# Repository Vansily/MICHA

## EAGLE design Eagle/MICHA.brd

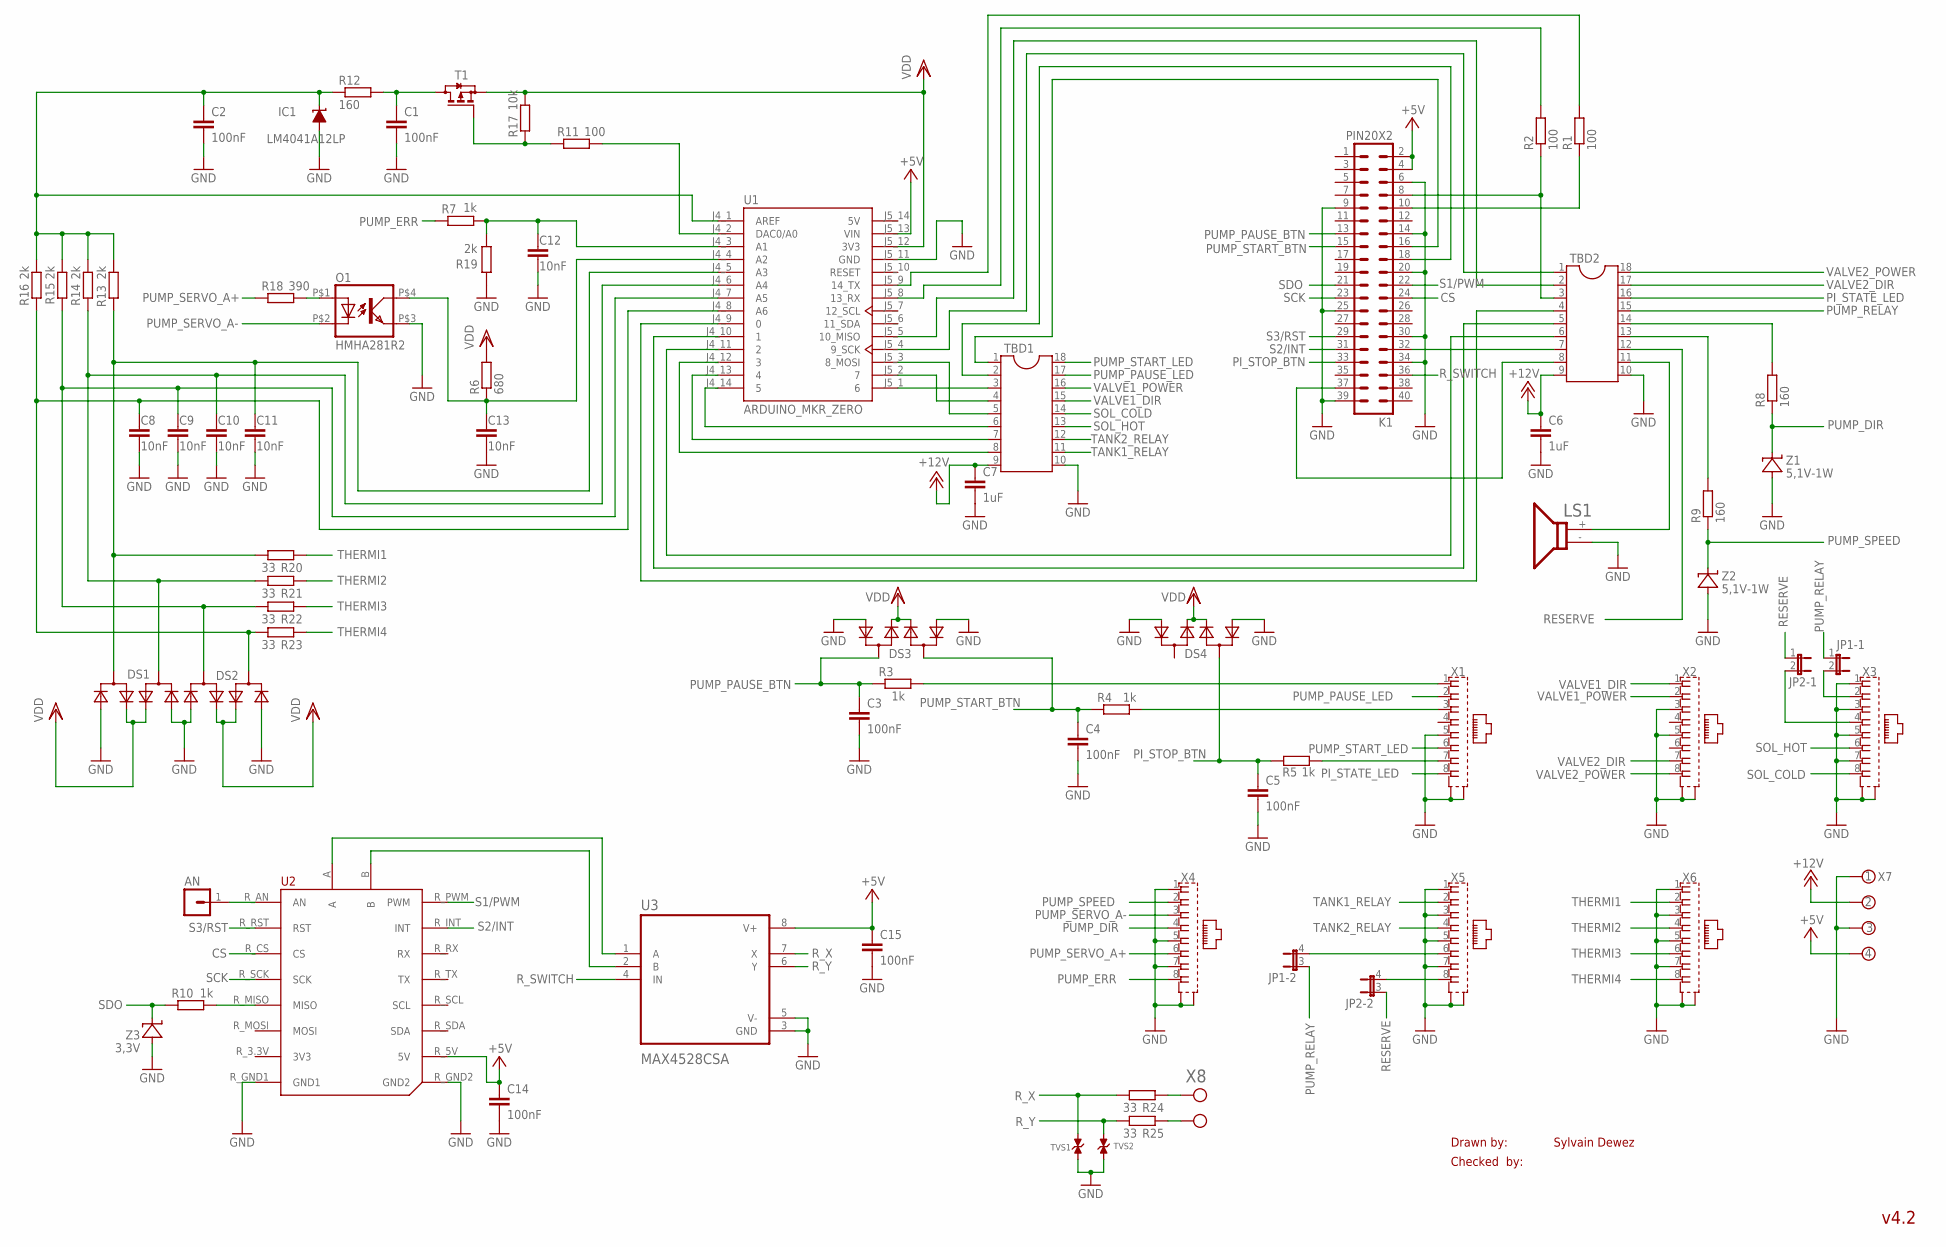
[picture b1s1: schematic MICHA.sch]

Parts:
AN: MA01_PINHEADER; MA01
C1, C2, C3, C4, C5, C14, C15: 100nF; C1206
C6, C7: 1uF; C1206
C8, C9, C10, C11, C12, C13: 10nF; C1206
DS1, DS2, DS3, DS4: SDM10M45SD; SDM10M45SD_SOT-26
IC1: LM4041A12LP; LP_O-PBCY-W3
JP1, JP2: JP2QE; JP2Q
K1: PIN20X2; PIN_20X2
LS1: RSPRO-BUZZER-7800743
O1: HMHA281R2
R1, R2, R11: 100; R1206
R3, R4, R5, R7, R10: 1k; R1206
R6: 680; R1206
R8, R9, R12: 160; R1206
R13, R14, R15, R16, R19: 2k; R1206
R17: 10k; R1206
R18: 390; R1206
R20, R21, R22, R23, R24, R25: 33; R1206
T1: BSS84; SOT23
TBD1, TBD2: DIL18S; SOCKET-18
TVS1, TVS2: TVS_SOD123
U1: ARDUINO_MKR_ZERO; MODULE_ARDUINO_MKR_ZERO
U2: MIKROE_CLICK_UPGRADE; MIKROE_BUS_MIDI_UPGRADE
U3: MAX4528CSA; SOIC127P600X175-8N
X1, X2, X3, X4, X5, X6: SS-7188S-A-NF_V2; BEL_SS-7188S-A-NF
X7: BUCHANAN_4_3.5MM
X8: MPT_0,5/_2-2,54_1725656_2; PH_MPT_0,5/_2-2,54_1725656
Z1, Z2: 5,1V-1W; ZENER_SMA
Z3: 3,3V; ZENER_SMA

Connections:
5V: U1.J5_14 (5V)
+5V: C14.1, C15.1, K1.2, K1.4, U1.J5_13 (VIN), U2.R_5V (5V), U3.8 (V+), X7.4 (KL3)
+12V: C6.1, C7.1, TBD1.9, TBD2.9, X7.2 (KL1)
CS: K1.24, U2.R_CS (CS)
D0: TBD2.4, U1.J4_9 (0)
D1: TBD2.5, U1.J4_10 (1)
D2: TBD2.6, U1.J4_11 (2)
D3: TBD1.8, U1.J4_12 (3)
D4: TBD1.7, U1.J4_13 (4)
D5: TBD1.6, U1.J4_14 (5)
D6: TBD1.3, U1.J5_1 (6)
D7: TBD1.4, U1.J5_2 (7)
D8: TBD1.5, U1.J5_3 (8_MOSI)
D9: TBD2.1, U1.J5_4 (9_SCK)
D10: TBD2.2, U1.J5_5 (10_MISO)
D19: C12.1, R7.2, R19.2, U1.J4_3 (A1)
D21: R11.2, U1.J4_2 (DAC0/A0)
GND: C1.2, C2.2, C3.2, C4.2, C5.2, C6.2, C7.2, C8.2, C9.2, C10.2, C11.2, C12.2, C13.2, C14.2, C15.2, DS1.1 (A2), DS1.4 (A3), DS2.1 (A2), DS2.4 (A3), DS3.1 (A2), DS3.4 (A3), DS4.1 (A2), DS4.4 (A3), IC1.3 (A), K1.6, K1.9, K1.14, K1.20, K1.25, K1.30, K1.34, K1.39, LS1.- (2), O1.P$3 (EMIT), R19.1, TBD1.10, TBD2.10, TVS1.P$2 (C1), TVS2.P$2 (C1), U1.J5_11 (GND), U2.R_GND1 (GND1), U2.R_GND2 (GND2), U3.3 (GND), U3.5 (V-), X1.5, X1.S1 (GND1), X1.S2 (GND2), X2.3, X2.5, X2.S1 (GND1), X2.S2 (GND2), X3.1, X3.3, X3.5, X3.7, X3.S1 (GND1), X3.S2 (GND2), X4.1, X4.5, X4.7, X4.S1 (GND1), X4.S2 (GND2), X5.1, X5.3, X5.5, X5.7, X5.S1 (GND1), X5.S2 (GND2), X6.1, X6.3, X6.5, X6.7, X6.S1 (GND1), X6.S2 (GND2), X7.1 (KL), X7.3 (KL2), Z1.A, Z2.A, Z3.A
unnamed: U2.B, U3.2 (B)
unnamed: R9.2, TBD2.13
unnamed: R11.1, R17.1, T1.1 (G)
unnamed: R8.2, TBD2.14
unnamed: R4.2, X1.3
unnamed: C2.1, IC1.2 (C), R12.1, R13.1, R14.1, R15.1, R16.1, U1.J4_1 (AREF)
unnamed: O1.P$1 (A), R18.2
unnamed: C1.1, R12.2, T1.3 (D)
unnamed: C13.1, O1.P$4 (COL), R6.1, U1.J4_4 (A2)
unnamed: U2.A, U3.1 (A)
unnamed: C11.1, DS1.3 (C1), R13.2, R20.1, U1.J4_5 (A3)
unnamed: C10.1, DS1.6 (C), R14.2, R21.1, U1.J4_6 (A4)
unnamed: C9.1, DS2.3 (C1), R15.2, R22.1, U1.J4_7 (A5)
unnamed: C8.1, DS2.6 (C), R16.2, R23.1, U1.J4_8 (A6)
unnamed: R10.2, U2.R_MISO (MISO)
unnamed: AN.1, U2.R_AN (AN)
unnamed: R24.2, X8.2 (KL1)
unnamed: R25.2, X8.1 (KL)
unnamed: JP1.4 (2), X5.6
unnamed: JP1.2, X3.2
unnamed: JP2.4 (2), X5.8
unnamed: JP2.2, X3.4
unnamed: R3.2, X1.1
unnamed: R5.2, X1.7
unnamed: LS1.+ (1), TBD2.11
PI16: K1.16, TBD1.1
PI18: K1.18, TBD1.2
PI32: K1.32, TBD2.7
PI33: K1.37, TBD2.8
PI_STATE_LED: TBD2.16, X1.8
PI_STOP_BTN: C5.1, DS4.3 (C1), K1.33, R5.1
PUMP_DIR: R8.1, X4.4, Z1.C
PUMP_ERR: R7.1, X4.8
PUMP_PAUSE_BTN: C3.1, DS3.6 (C), K1.13, R3.1
PUMP_PAUSE_LED: TBD1.17, X1.2
PUMP_RELAY: JP1.1, JP1.3 (1), TBD2.15
PUMP_SERVO_A+: R18.1, X4.6
PUMP_SERVO_A-: O1.P$2 (C), X4.3
PUMP_SPEED: R9.1, X4.2, Z2.C
PUMP_START_BTN: C4.1, DS3.3 (C1), K1.15, R4.1
PUMP_START_LED: TBD1.18, X1.6
RESERVE: JP2.1, JP2.3 (1), TBD2.12
RX_A: R2.2, U1.J5_8 (13_RX)
RX_PI: K1.10, R1.1
R_SWITCH: K1.36, U3.4 (IN)
R_X: R24.1, TVS1.P$1 (C), U3.7 (X)
R_Y: R25.1, TVS2.P$1 (C), U3.6 (Y)
S1/PWM: K1.22, U2.R_PWM (PWM)
S2/INT: K1.31, U2.R_INT (INT)
S3/RST: K1.29, U2.R_RST (RST)
SCK: K1.23, U2.R_SCK (SCK)
SDO: K1.21, R10.1, Z3.C
SOL_COLD: TBD1.14, X3.8
SOL_HOT: TBD1.13, X3.6
TANK1_RELAY: TBD1.11, X5.2
TANK2_RELAY: TBD1.12, X5.4
THERMI1: R20.2, X6.2
THERMI2: R21.2, X6.4
THERMI3: R22.2, X6.6
THERMI4: R23.2, X6.8
TX_A: R1.2, U1.J5_9 (14_TX)
TX_PI: K1.8, R2.1, TBD2.3
VALVE1_DIR: TBD1.15, X2.1
VALVE1_POWER: TBD1.16, X2.2
VALVE2_DIR: TBD2.17, X2.7
VALVE2_POWER: TBD2.18, X2.8
VDD: DS1.2 (A1), DS1.5 (A4), DS2.2 (A1), DS2.5 (A4), DS3.2 (A1), DS3.5 (A4), DS4.2 (A1), DS4.5 (A4), R6.2, R17.2, T1.2 (S), U1.J5_12 (3V3)

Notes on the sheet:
Drawn by:
Checked by:
Sylvain Dewez
v4.2

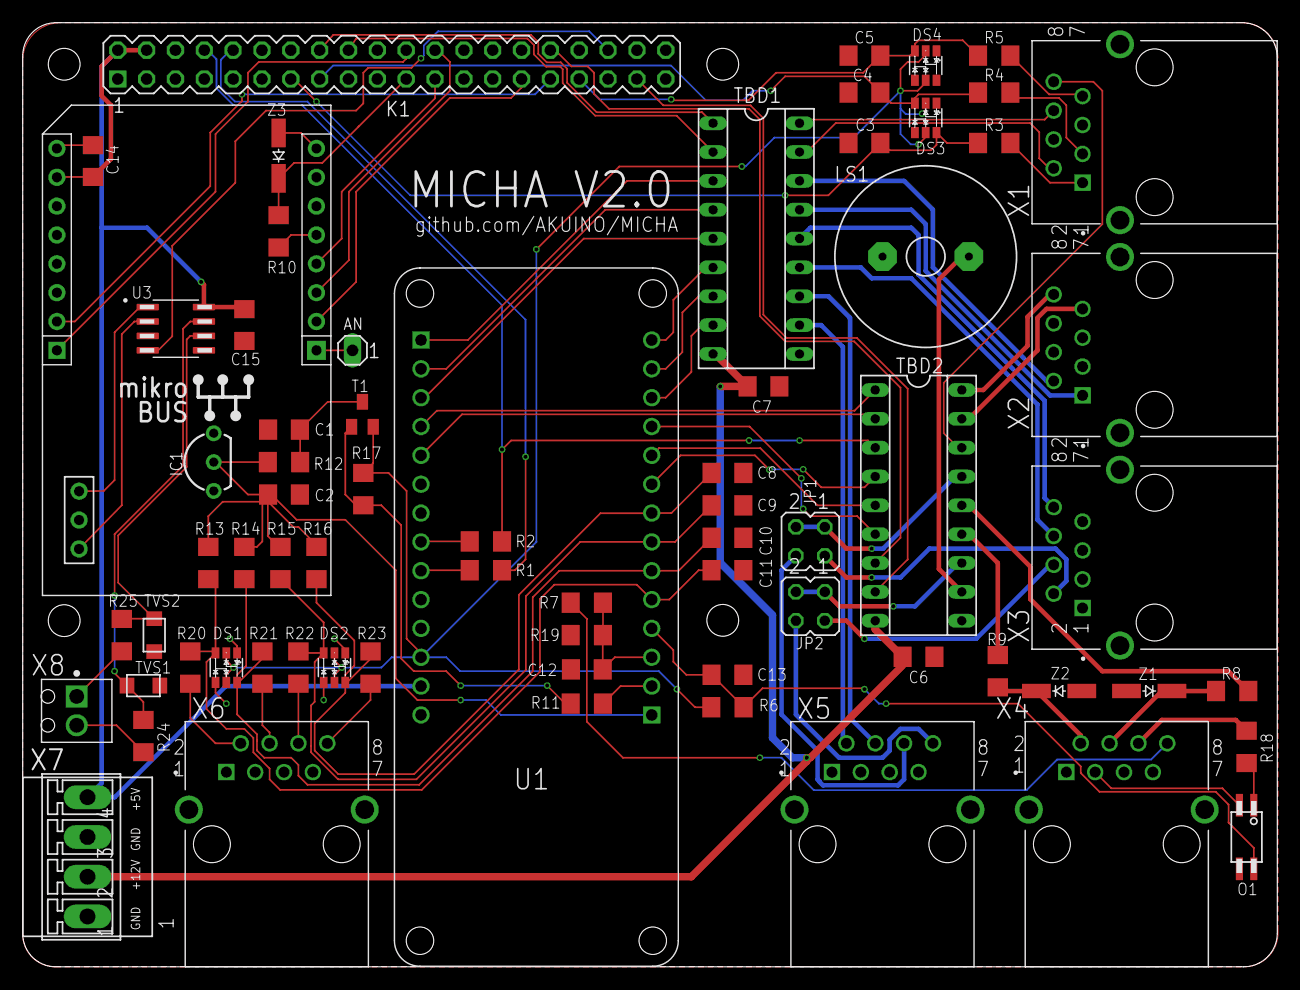
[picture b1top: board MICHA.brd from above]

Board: 2 copper layers, 110.5 x 83.1 mm, 70 parts (0 on the bottom side), 84 nets.

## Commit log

2021-04-06 Renommage
    Renommage du dossier MICHA_v0.3.3 ainsi que de son fichier en MICHA
2021-04-06 Màj code Arduino MICHA
    Mise à jour du code MICHA (v1.0.0)
2021-04-06 Màj registres
    Ajout d'un registre pour stocker l'incrémentation par défaut de la vitesse
2021-04-06 Pump speed pin modification
2021-04-06 Add auto-test mode
2021-11-05 Sauvegarde
    Sauvegarde du code MICHA tournant dans le pasteurisateur actuellement (5 novembre 2021).
2021-11-05 MICHAv2.0
    Version 2.0 de MICHA
